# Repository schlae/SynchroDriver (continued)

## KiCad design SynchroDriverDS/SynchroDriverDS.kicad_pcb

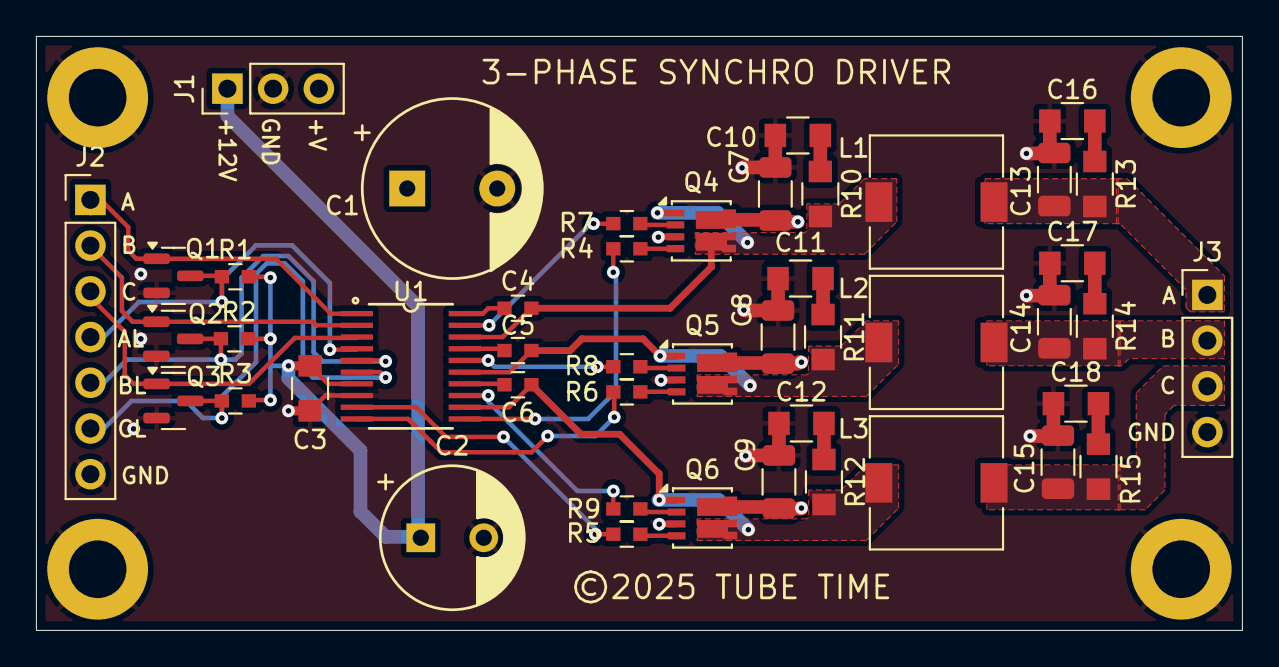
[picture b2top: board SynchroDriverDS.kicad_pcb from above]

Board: 2 copper layers, 67.0 x 33.0 mm, 50 parts (0 on the bottom side), 36 nets.

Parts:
C1: 1000uF; CAPAE500P1000X1500
C2: 100uF; CAPAE350P800X700
C3: 1uF; CAPC2012X55
C4, C5, C6: 0.1uF; CAPC1608X100
C7, C8, C9, C13, C14, C15: 10uF; C_1206_3216Metric
C10, C11, C12, C16, C17, C18: DNI; CAPC2012X55
H1, H2, H3, H4: MountingHole_Pad; MountingHole_3.2mm_M3_DIN965_Pad
J1: POWER; PinHeader_1x03_P2.54mm_Vertical
J2: CTRL; PinHeader_1x07_P2.54mm_Vertical
J3: Conn_01x04; PinHeader_1x04_P2.54mm_Vertical
L1, L2, L3: 220uH; L_7.3x7.3_H3.5
Q1, Q2, Q3: 2N7002; SOT-23
Q4, Q5, Q6: SIS990; Vishay_PowerPAK_1212-8_Dual
R1, R2, R3: 4.7K; RESC1608X55
R4, R5, R6, R7, R8, R9: 1; RESC1608X55
R10, R11, R12, R13, R14, R15: DNI; RESC2012X55
U1: DRV8300; TSOP65P640X110-20

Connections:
+12V: C2.1, C3.1, J1.1, R1.2, R2.2, R3.2, U1.7 (GVDD)
+36V: C1.1, C7.1, C8.1, C9.1, J1.3, Q4.6 (D), Q5.6 (D), Q6.6 (D)
/SingleSynchroDriver/INA: J2.1, Q1.1 (G), U1.1 (INHA)
/SingleSynchroDriver/INAL: J2.4, Q1.3 (D), R1.1, U1.4 (INLA)
/SingleSynchroDriver/INB: J2.2, Q2.1 (G), U1.2 (INHB)
/SingleSynchroDriver/INBL: J2.5, Q2.3 (D), R2.1, U1.5 (INLB)
/SingleSynchroDriver/INC: J2.3, Q3.1 (G), U1.3 (INHC)
/SingleSynchroDriver/INCL: J2.6, Q3.3 (D), R3.1, U1.6 (INLC)
/SingleSynchroDriver/PHASE_A_OUT: C13.1, J3.1, L1.2, R13.1
/SingleSynchroDriver/PHASE_B_OUT: C14.1, J3.2, L2.2, R14.1
/SingleSynchroDriver/PHASE_C_OUT: C15.1, J3.3, L3.2, R15.1
GND: C1.2, C2.2, C3.2, C7.2, C8.2, C9.2, C10.2, C11.2, C12.2, C13.2, C14.2, C15.2, C16.2, C17.2, C18.2, H1.1, H2.1, H3.1, H4.1, J1.2, J2.7, J3.4, Q1.2 (S), Q2.2 (S), Q3.2 (S), Q4.3 (S), Q5.3 (S), Q6.3 (S), U1.8 (GND)
unnamed: C10.1, R10.2
unnamed: C11.1, R11.2
unnamed: C12.1, R12.2
unnamed: C16.1, R13.2
unnamed: C17.1, R14.2
unnamed: C18.1, R15.2
unnamed: Q4.2 (G), R7.2
unnamed: C4.2, L1.1, Q4.1 (S), Q4.5 (D), R10.1, U1.18 (SHA)
unnamed: Q4.4 (G), R4.2
unnamed: Q5.2 (G), R8.2
unnamed: C5.2, L2.1, Q5.1 (S), Q5.5 (D), R11.1, U1.15 (SHB)
unnamed: Q5.4 (G), R6.2
unnamed: Q6.2 (G), R9.2
unnamed: C6.2, L3.1, Q6.1 (S), Q6.5 (D), R12.1, U1.12 (SHC)
unnamed: Q6.4 (G), R5.2
unnamed: C4.1, U1.20 (BSTA)
unnamed: C5.1, U1.17 (BSTB)
unnamed: C6.1, U1.14 (BSTC)
unnamed: R7.1, U1.19 (GHA)
unnamed: R8.1, U1.16 (GHB)
unnamed: R9.1, U1.13 (GHC)
unnamed: R4.1, U1.11 (GLA)
unnamed: R6.1, U1.10 (GLB)
unnamed: R5.1, U1.9 (GLC)

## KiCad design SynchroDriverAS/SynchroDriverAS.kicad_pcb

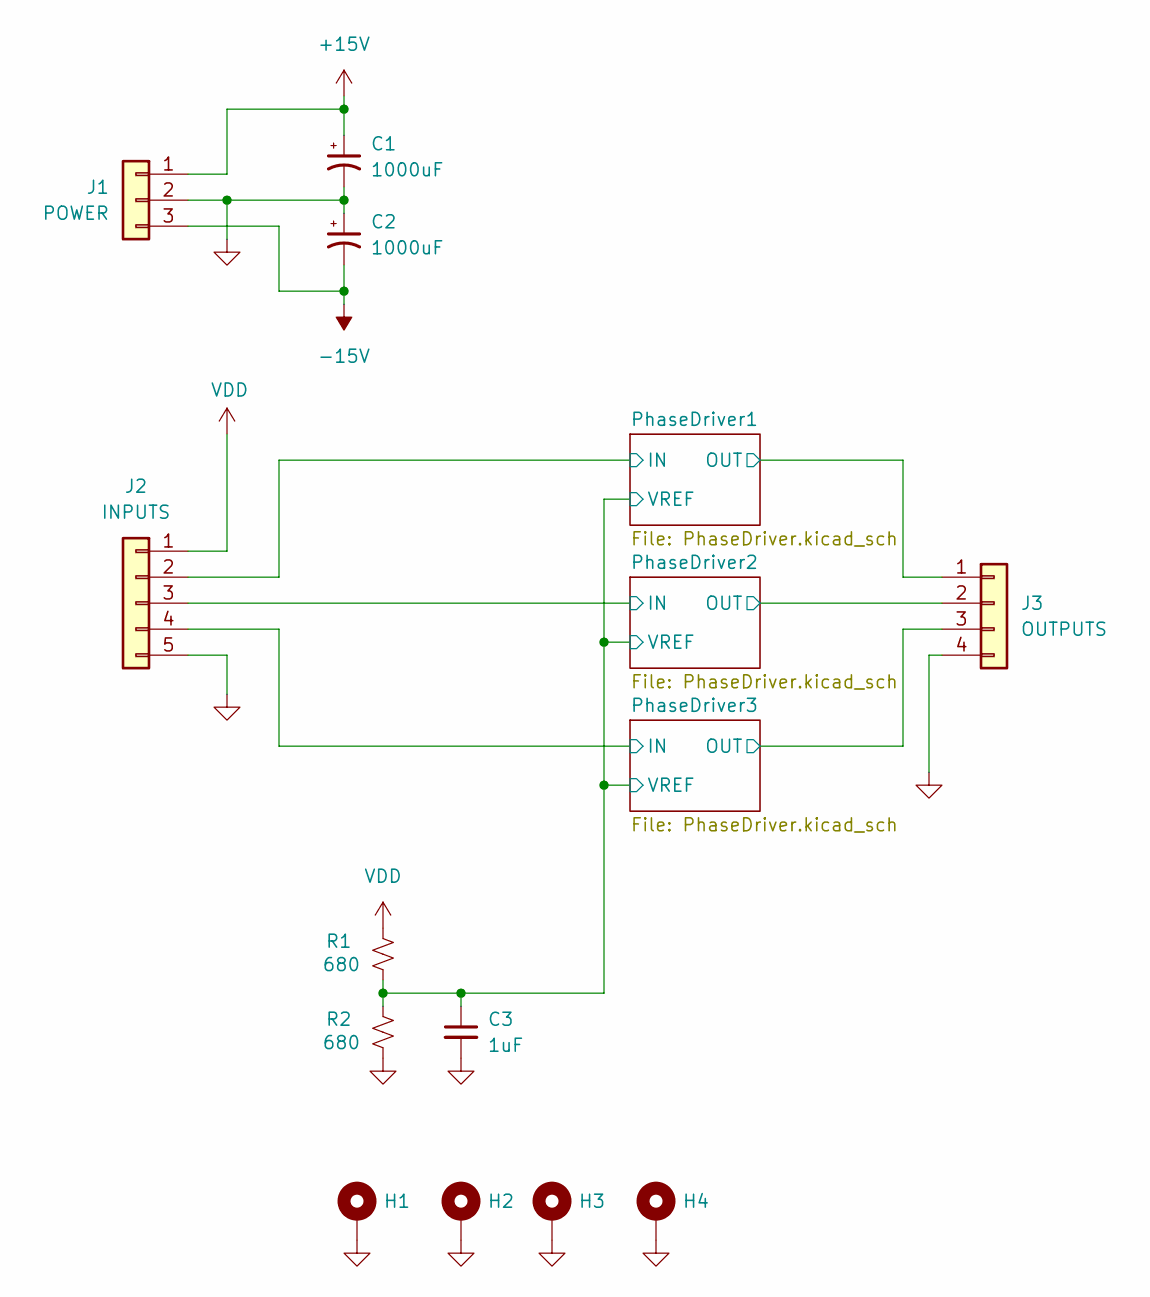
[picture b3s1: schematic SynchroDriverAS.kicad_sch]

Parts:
C1, C2: 1000uF; CAPAE500P1000X1500
C3: 1uF; CAPC2012X55
H1, H2, H3, H4: MountingHole_Pad; MountingHole_3.2mm_M3_DIN965_Pad
J1: POWER; PinHeader_1x03_P2.54mm_Vertical
J2: INPUTS; PinHeader_1x05_P2.54mm_Vertical
J3: OUTPUTS; PinHeader_1x04_P2.54mm_Vertical
R1, R2: 680; RESC1608X55

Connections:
+15V: C1.1, J1.1; also elsewhere on the board
-15V: C2.2, J1.3; also elsewhere on the board
/PhaseDriver1/IN: J2.2; also elsewhere on the board
/PhaseDriver1/OUT: J3.1; also elsewhere on the board
/PhaseDriver1/VREF: C3.1, R1.1, R2.2; also elsewhere on the board
/PhaseDriver2/IN: J2.3; also elsewhere on the board
/PhaseDriver2/OUT: J3.2; also elsewhere on the board
/PhaseDriver3/IN: J2.4; also elsewhere on the board
/PhaseDriver3/OUT: J3.3; also elsewhere on the board
GND: C1.2, C2.1, C3.2, H1.1, H2.1, H3.1, H4.1, J1.2, J2.5, J3.4, R2.1; also elsewhere on the board
VDD: J2.1, R1.2

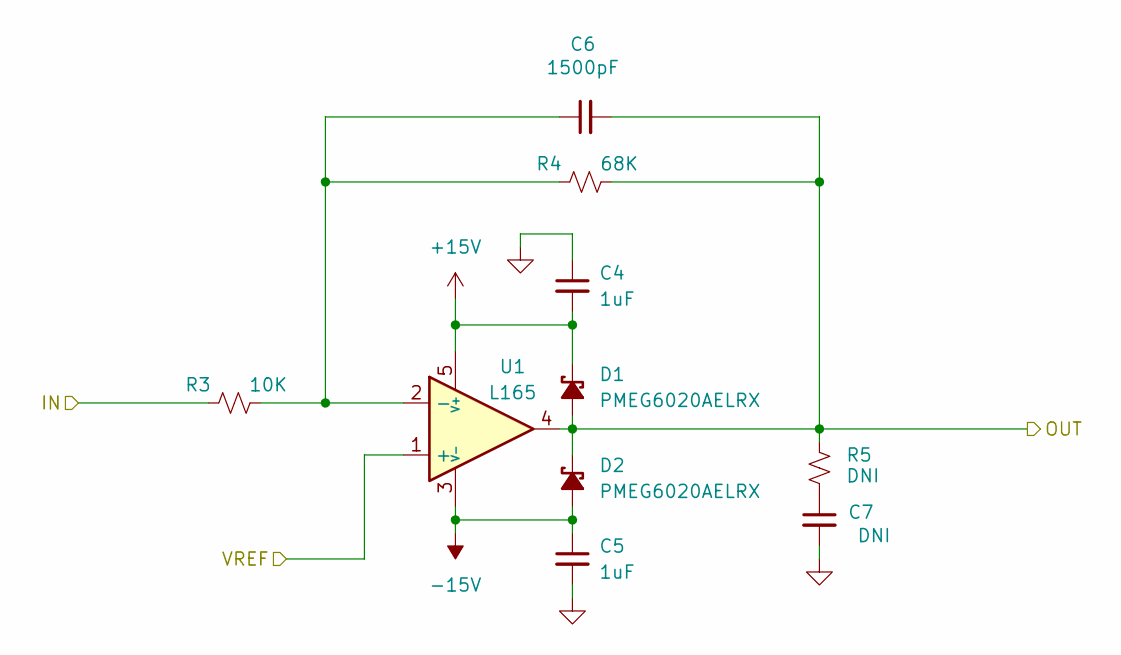
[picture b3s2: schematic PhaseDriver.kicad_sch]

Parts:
C4, C5: 1uF; CAPC2012X55
C6: 1500pF; CAPC1608X100
C7: DNI; CAPC2012X55
D1, D2: PMEG6020AELRX; SOD3716X117; Mouser 771-PMEG10010ELRX
R3: 10K; RESC1608X55
R4: 68K; RESC1608X55
R5: DNI; RESC2012X55
U1: L165; TO-220-5_Stagger_Vertical_L165

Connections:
+15V: C4.2, D1.1 (K), U1.5 (V+); also elsewhere on the board
-15V: C5.1, D2.2 (A), U1.3 (V-); also elsewhere on the board
/PhaseDriver1/IN: R3.1; also elsewhere on the board
/PhaseDriver1/OUT: C6.2, D1.2 (A), D2.1 (K), R4.2, R5.1, U1.4; also elsewhere on the board
/PhaseDriver1/VREF: U1.1 (+); also elsewhere on the board
GND: C4.1, C5.2, C7.2; also elsewhere on the board
unnamed: C7.1, R5.2
unnamed: C6.1, R3.2, R4.1, U1.2 (-)

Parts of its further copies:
C8, C9, C12, C13: 1uF; CAPC2012X55
C10, C14: 1500pF; CAPC1608X100
C11, C15: DNI; CAPC2012X55
D3, D4, D5, D6: PMEG6020AELRX; SOD3716X117; Mouser 771-PMEG10010ELRX
R6, R9: 10K; RESC1608X55
R7, R10: 68K; RESC1608X55
R8, R11: DNI; RESC2012X55
U2, U3: L165; TO-220-5_Stagger_Vertical_L165

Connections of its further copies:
+15V: C8.2, C12.2, D3.1 (K), D5.1 (K), U2.5 (V+), U3.5 (V+); also elsewhere on the board
-15V: C9.1, C13.1, D4.2 (A), D6.2 (A), U2.3 (V-), U3.3 (V-); also elsewhere on the board
/PhaseDriver1/VREF: U2.1 (+), U3.1 (+); also elsewhere on the board
/PhaseDriver2/IN: R6.1; also elsewhere on the board
/PhaseDriver2/OUT: C10.2, D3.2 (A), D4.1 (K), R7.2, R8.1, U2.4; also elsewhere on the board
/PhaseDriver3/IN: R9.1; also elsewhere on the board
/PhaseDriver3/OUT: C14.2, D5.2 (A), D6.1 (K), R10.2, R11.1, U3.4; also elsewhere on the board
GND: C8.1, C9.2, C11.2, C12.1, C13.2, C15.2; also elsewhere on the board
unnamed: C11.1, R8.2
unnamed: C15.1, R11.2
unnamed: C10.1, R6.2, R7.1, U2.2 (-)
unnamed: C14.1, R9.2, R10.1, U3.2 (-)

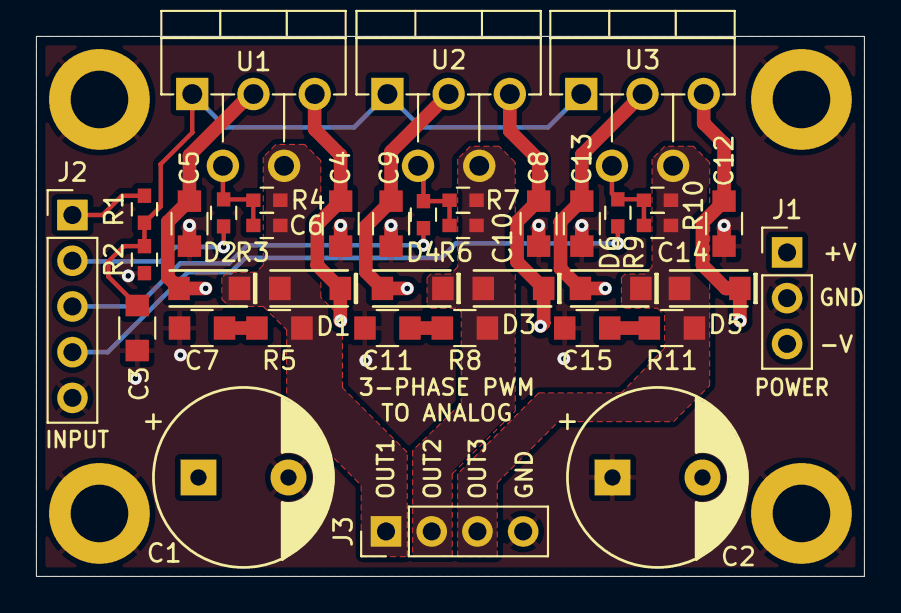
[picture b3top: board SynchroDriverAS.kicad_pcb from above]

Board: 2 copper layers, 46.0 x 30.0 mm, 42 parts (0 on the bottom side), 17 nets.

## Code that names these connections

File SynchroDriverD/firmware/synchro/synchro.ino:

/**
 * Driver for TubeTime's synchro board.
 * Ken Shirriff, righto.com
*/

IntervalTimer myTimer; // Interrupt to update the PWM levels

volatile unsigned long count = 0; // Index into the sine wave

// Analog inputs from pots
#define ROLL A0
#define PITCH A1
#define YAW A2
#define ROLL_RATE A3
#define PITCH_RATE A4
#define YAW_RATE A5
#define ROLL_ERR A6
#define PITCH_ERR A7
#define YAW_ERR A8

// Outputs
#define PWM_R0 0
#define PWM_R1 1
#define PWM_R2 2
#define PWM_P0 3
#define PWM_P1 4
#define PWM_P2 5
#define PWM_Y0 6
#define PWM_Y1 7
#define PWM_Y2 8
#define PWM_RR 9
#define PWM_RE 10
#define PWM_PR 11
#define PWM_PE 12
#define PWM_YR 24
#define PWM_YE 25
#define FLAG 26

// Sync input
#define SYNC 30

// Sine wave, arbitrarily 100 samples long.
float sine[100] = {
  0.0000,
  0.0628,
  0.1253,
  0.1874,
  0.2487,
  0.3090,
  0.3681,
  0.4258,
  0.4818,
  0.5358,
  0.5878,
  0.6374,
  0.6845,
  0.7290,
  0.7705,
  0.8090,
  0.8443,
  0.8763,
  0.9048,
  0.9298,
  0.9511,
  0.9686,
  0.9823,
  0.9921,
  0.9980,
  1.0000,
  0.9980,
  0.9921,
  0.9823,
  0.9686,
  0.9511,
  0.9298,
  0.9048,
  0.8763,
  0.8443,
  0.8090,
  0.7705,
  0.7290,
  0.6845,
  0.6374,
  0.5878,
  0.5358,
  0.4818,
  0.4258,
  0.3681,
  0.3090,
  0.2487,
  0.1874,
  0.1253,
  0.0628,
  0.0000,
  -0.0628,
  -0.1253,
  -0.1874,
  -0.2487,
  -0.3090,
  -0.3681,
  -0.4258,
  -0.4818,
  -0.5358,
  -0.5878,
  -0.6374,
  -0.6845,
  -0.7290,
  -0.7705,
  -0.8090,
  -0.8443,
  -0.8763,
  -0.9048,
  -0.9298,
  -0.9511,
  -0.9686,
  -0.9823,
  -0.9921,
  -0.9980,
  -1.0000,
  -0.9980,
  -0.9921,
  -0.9823,
  -0.9686,
  -0.9511,
  -0.9298,
  -0.9048,
  -0.8763,
  -0.8443,
  -0.8090,
  -0.7705,
  -0.7290,
  -0.6845,
  -0.6374,
  -0.5878,
  -0.5358,
  -0.4818,
  -0.4258,
  -0.3681,
  -0.3090,
  -0.2487,
  -0.1874,
  -0.1253,
  -0.0628,
};

// Port tables

#define N_AIN 9
#define NEEDLE_OFFSET 3
const int ainputs[N_AIN] = { ROLL, PITCH, YAW, ROLL_RATE, PITCH_RATE, YAW_RATE, ROLL_ERR, PITCH_ERR, YAW_ERR };

#define N_SYNCHRO 9
const int synchroOutputs[N_SYNCHRO] = { PWM_R0, PWM_R1, PWM_R2, PWM_P0, PWM_P1, PWM_P2, PWM_Y0, PWM_Y1,
                                        PWM_Y2 };
#define N_OTHER 7
const int otherOutputs[N_OTHER] = { PWM_RR, PWM_RE, PWM_PR, PWM_PE, PWM_YR, PWM_YE, FLAG };

// Magnitudes for the 400 Hz PWM outputs
volatile float mag[N_SYNCHRO] = { 0 };

// Interrupt handler
void update() {
  for (int i = 0; i < N_SYNCHRO; i++) {
    analogWrite(synchroOutputs[i], int(sine[count] * mag[i] * 120 + 120));
  }
  count = (count + 1) % 100;
}

// Sync interrupt
void syncInterrupt() {
  if (count < 20 || count > 80) { // Ignore sync if it is wildly off
      count = 0; // Reset the counter on rising edge of sync input
  }
}

void setup() {
  pinMode(SYNC, INPUT);

  // Initialize analog inputs
  for (int i = 0; i < N_AIN; i++) {
    pinMode(ainputs[i], INPUT);
  }

  // Initialize PWM outputs
  for (int i = 0; i < N_SYNCHRO; i++) {
    pinMode(synchroOutputs[i], OUTPUT);
    analogWriteFrequency(synchroOutputs[i], 15000000 / 64);  // divide by 64 for 8-bit resolution
  }
  for (int i = 0; i < N_OTHER; i++) {
    pinMode(otherOutputs[i], OUTPUT);
    analogWriteFrequency(otherOutputs[i], 15000000 / 64);
  }
  digitalWrite(FLAG, 1);

  myTimer.begin(update, 25); // 25 microseconds * 100 samples give 400 Hz

  attachInterrupt(digitalPinToInterrupt(SYNC), syncInterrupt, RISING);
}

int sync = 0; // Track the sync input

void loop() {

  // Synchro outputs. Set them according to the pot inputs
  for (int i = 0; i < 3; i++) {
    float ang = analogRead(ainputs[i]) / 1024. * 2 * PI;
    float m0 = (sin(ang) + 1) / 2;
    float m1 = (sin(ang + 2 * PI / 3) + 1) / 2;
    float m2 = (sin(ang + 4 * PI / 3) + 1) / 2;
    noInterrupts();
    mag[3 * i] = m0;
    mag[3 * i + 1] = m1;
    mag[3 * i + 2] = m2;
    interrupts();
  }
  // Needle analog outputs, -3 to +3, according to pot inputs
  for (int i = 0; i < 6; i++) {
    // Read is 0 to 1023, write is 0 to 255
    int input = analogRead(ainputs[i + NEEDLE_OFFSET]) / 4;
    analogWrite(otherOutputs[i], input);
  }

}

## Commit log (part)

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2025-06-29 Ad flag drive circuit
2025-07-06 PCB layout
2025-07-06 Mouser parts, layout changes
2025-07-07 Complete layout
2025-07-07 Layout for analog 3-phase pcb
2025-07-08 Update digital single synchro pcb
2025-07-13 Swap DRV8300 for DRV8300DI, change ref in
2025-07-17 Improve ref in, clearance for 115V
2025-08-07 Fab out and add schematic pdf
2025-08-29 Tweaks after first build
2025-09-08 Add Teensy firmware
2025-09-13 Firmware PWM frequency fix. Synchro bodge. Needle value changes
2025-09-13 Meter driver vref fix. Sync in gain fix.
2025-10-06 Move synchro.ino to subdirectory. The Arduino IDE requires the file to be in a directory with the same name.
2025-10-26 Copy good synchro.ino to synchroDemo.ino before changing.
2025-10-26 Autoformatter
2025-10-26 Implement the demo code to move ball and needles sinusoidally.
2025-10-26 Fix int/float bug
2025-11-02 Initialize axis and needle values. Pull out axis code. Change analog initialization to exclude FLAG. Reduce needle amplitude by 50%.
2025-11-02 Clone demo to make a second demo.
2025-11-02 Take FLAG out of analog output list.
2025-11-02 Rename directory, removing capital
2025-11-02 Clone synchroDemo before modifying it.
2025-11-02 Update second demo to move multiple axes and needles at the same time.
2025-11-02 Typo
2025-12-05 Copy of synchroDemo2.ino before changes.
2025-12-05 FDAI driver board program to get roll, pitch, and yaw from serial port.
2025-12-05 Program to parse flight log and send roll, pitch, and yaw over serial port.
2025-12-05 Creates a simulated flight log for testing.
2025-12-08 Handle optional trailing comma on yaw
2025-12-08 Hardcode the flight data
2026-01-04 Add interpolation.
2026-01-04 Program to test alignment by moving each axis +/- 30 degrees separately.
2026-01-05 Add correction factors to the angles. Swap pitch and yaw and make yaw negative.
2026-01-05 Add angle adjustments to flightpath. Set initial yaw to 0 by subtracting yaw at start. Wait three seconds before starting flightpath.
2026-01-05 Fix interpolation glitch when angle wraps around. Formerly, interpolating between 359 degrees and 1 would go through 180. Now the interpolation will go the "short" way through 0.
2026-03-14 add level shifter and fuses
2026-03-14 swap level shifter
2026-06-24 Wire up new level shifters, add motor diode
